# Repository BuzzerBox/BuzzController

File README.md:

# BuzzController

Firmware and hardware designs for the BuzzerBox — a 10-button quiz buzzer controller. A Raspberry Pi CM4 acts as the host, communicating with an ATmega328P co-processor over serial. The ATmega handles button detection, locks the active buzzer, and drives a 7-segment display.

[`wireless/`](wireless/README.md) holds the firmware of the wireless buzzer: a battery-powered ESP32 Feather V2 that joins the box's WiFi.

---

## Features

- **10 buzzers** with individual LED feedback, interrupt-driven detection
- **7-segment display** showing the active buzzer number and RPi connection status
- **Serial communication** with a Raspberry Pi at 115200 baud, including heartbeat monitoring
- **Soft release** — RPi can remotely unlock the selected buzzer
- **Watchdog timer** for automatic recovery from firmware hangs
- **I2C I/O expanders** (MCP23017) to drive LEDs and display

---

## Repository Structure

```
BuzzController/
├── cad/
│   └── BuzzerBox/
│       ├── controller.brd/.sch    # Main ATmega328P controller board
│       ├── xlrpcb.brd/.sch        # XLR connector board (V3)
│       ├── devkeys.brd/.sch       # Development key PCB
│       ├── ttl_adapter.brd/.sch   # TTL adapter for devkit
│       └── eagle.epf              # EAGLE CAD project file
│   └── BuzzerBoxPanel.f3d         # Fusion 360 enclosure design
├── wireless/                      # Wireless buzzer (ESP32 Feather V2), see wireless/README.md
└── code/
    ├── platformio.ini             # Build configuration
    └── src/
        ├── BuzzerBox.cpp          # Main firmware logic
        ├── i2c_communication.*    # MCP23017 I/O expander driver
        ├── rpi_communication.*    # Serial protocol with Raspberry Pi
        ├── 7segment.*             # 7-segment display driver
        └── portConfig.hpp         # Pin/port and I2C address configuration
```

---

## Hardware

| Component | Details |
|---|---|
| Host | Raspberry Pi CM4 (mounted directly on PCB) |
| Microcontroller | ATmega328P |
| I/O Expanders | 2× MCP23017 (I2C addresses `0x20`, `0x21`) |
| Display | 7-segment LED (common cathode, via expander) |
| Buttons | 10 buzzers across MCU ports B, C, D + 1 release button |
| CM4 ↔ MCU | Serial UART (115200 baud) |
| Programming | AVRISP mkII compatible (e.g. Olimex AVR-ISP-MK2) via the 6-pin ICSP header |

PCB designs are in [EAGLE](https://www.autodesk.com/products/eagle/overview) format. The enclosure panel is a [Fusion 360](https://www.autodesk.com/products/fusion-360/overview) file.

---

## Serial Protocol

Communication between the ATmega328P and the Raspberry Pi uses 3-byte UART messages at **115200 baud**:

```
[Command Byte] [Data Byte] [0xFF]
```

### Commands (RPi → Controller)

| Command | Value | Description |
|---|---|---|
| `EMPTY` | `0x00` | No operation |
| `SOFT_RELEASE` | `0x01` | Unlock the active buzzer |
| `SET_BUZZER` | `0x02` | Lock a specific buzzer (data = buzzer ID 0–9) |

### Events (Controller → RPi)

| Event | Byte | Description |
|---|---|---|
| Button pressed | `'0'`–`'9'` (ASCII) | Buzzer ID of the pressed button |
| Buzzer unlocked | `'q'` | Acknowledges an unlock |

A heartbeat is expected from the RPi every **6 seconds**. If no heartbeat is received within this window, the controller transitions to a disconnected state and reflects this on the display's decimal point.

---

## Building and Flashing

The firmware uses [PlatformIO](https://platformio.org/).

```bash
# Install PlatformIO CLI or use the VSCode extension

# Build
pio run

# Upload
pio run --target upload
```

Upload uses an AVRISP mkII compatible programmer (e.g. Olimex AVR-ISP-MK2) over USB, connected to the 6-pin ICSP header. Power the board from its own supply while flashing.

---

## Development

The `devkeys` PCB and `ttl_adapter` PCB are development accessories for testing the firmware without the full buzzer assembly.

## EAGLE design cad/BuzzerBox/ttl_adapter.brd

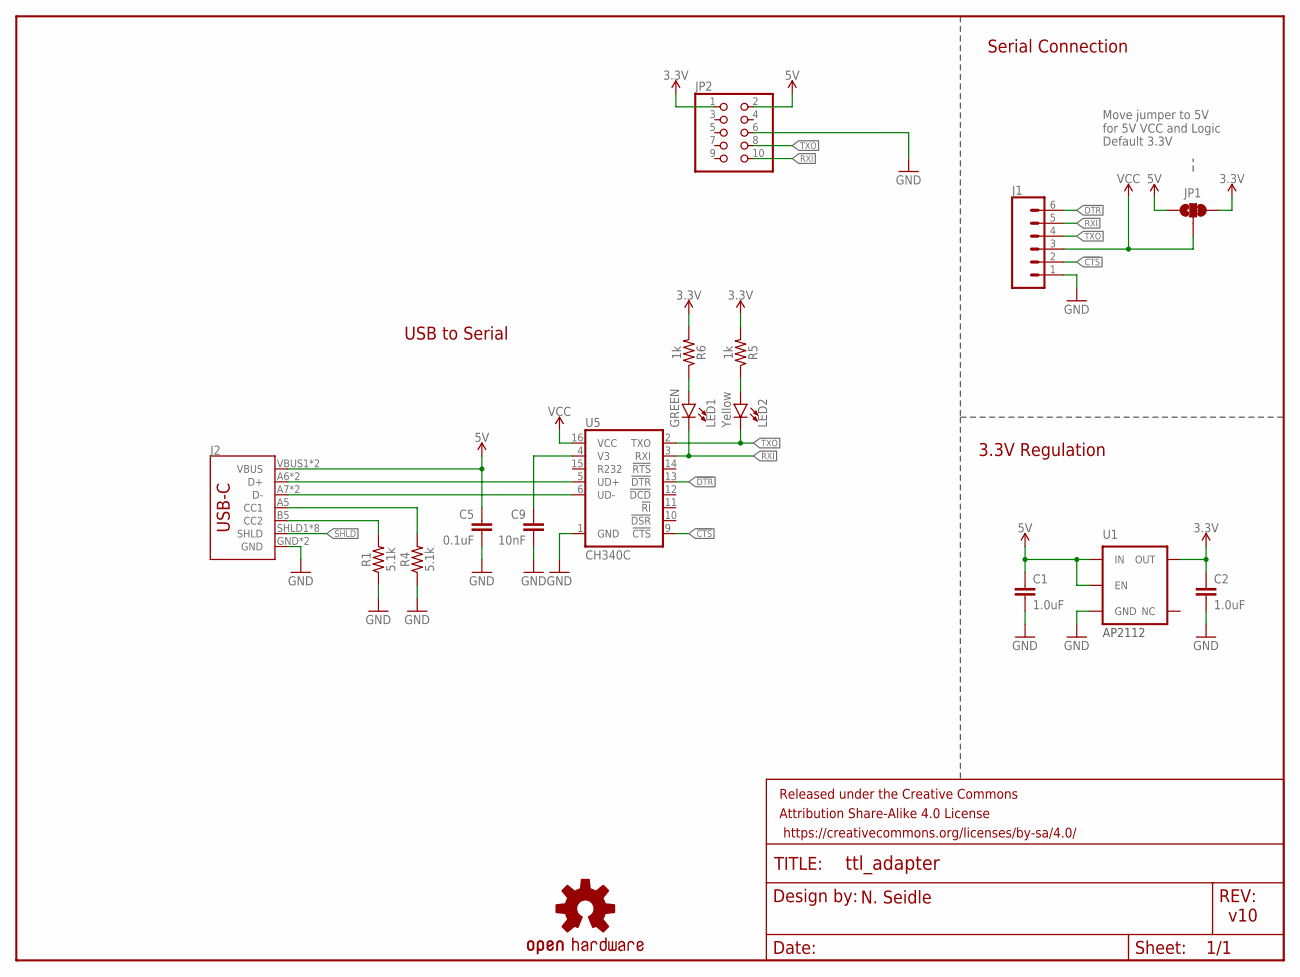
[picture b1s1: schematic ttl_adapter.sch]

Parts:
C1, C2: 1.0uF; 0603
C5: 0.1uF; 0603
C9: 10nF; 0603
FRAME1: FRAME-LETTER; CREATIVE_COMMONS
J1: CONN_06SMD-FEMALE-V2; 1X06-SMD-FEMALE
J2: USB_C16PIN; USB-C-16P
JP1: JUMPER-SMT_3_1-NC_TRACE_SILK; SMT-JUMPER_3_1-NC_TRACE_SILK
JP2: PINHD-2X5; 2X05
LED1: GREEN; LED-0603
LED2: Yellow; LED-0603
LOGO1: OSHW-LOGOS; OSHW-LOGO-S
R1, R4: 5.1k; 0603
R5, R6: 1k; 0603
U1: 3.3V; SOT23-5
U5: CH340C; SO016

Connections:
3.3V: C2.1, JP1.3, JP2.1, R5.2, R6.2, U1.5 (OUT)
5V: C1.1, C5.1, J2.VBUS1 (VBUS), J2.VBUS2 (VBUS), JP1.1, JP2.2, U1.1 (IN), U1.3 (EN)
!CTS: J1.2, U5.9 (!CTS)
!DTR: J1.6, U5.13 (!DTR)
CC1: J2.A5 (CC1), R4.2
CC2: J2.B5 (CC2), R1.2
D+: J2.A6 (D+), J2.B6 (D+), U5.5 (UD+)
D-: J2.A7 (D-), J2.B7 (D-), U5.6 (UD-)
GND: C1.2, C2.2, C5.2, C9.2, J1.1, J2.GND, J2.GND2 (GND), JP2.6, R1.1, R4.1, U1.2 (GND), U5.1 (GND)
unnamed: C9.1, U5.4 (V3)
unnamed: LED1.A, R6.1
unnamed: LED2.A, R5.1
RXI: J1.5, JP2.10, LED1.C, U5.3 (RXI)
SHLD: J2.SHLD1 (SHLD), J2.SHLD2 (SHLD), J2.SHLD3 (SHLD), J2.SHLD4 (SHLD), J2.SHLD5 (SHLD), J2.SHLD6 (SHLD), J2.SHLD7 (SHLD), J2.SHLD8 (SHLD)
TXO: J1.4, JP2.8, LED2.C, U5.2 (TXO)
VCC: J1.3, JP1.2, U5.16 (VCC)

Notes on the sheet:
Default 3.3V
v10
USB to Serial
3.3V Regulation
N. Seidle
Move jumper to 5V for 5V VCC and Logic
Serial Connection
AP2112

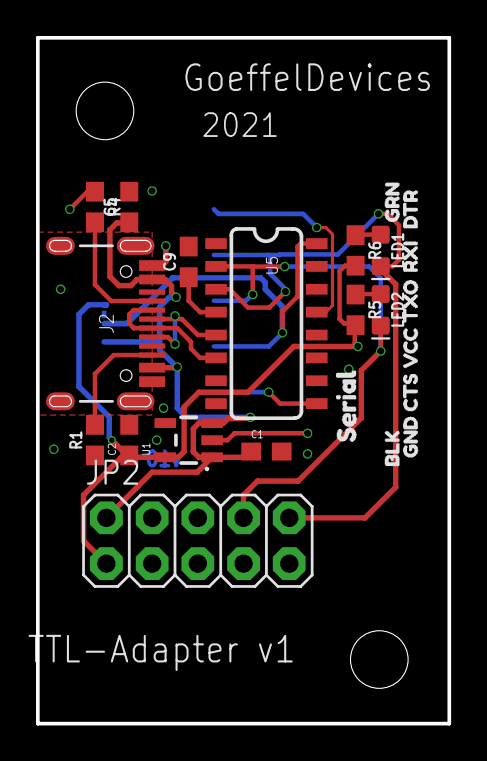
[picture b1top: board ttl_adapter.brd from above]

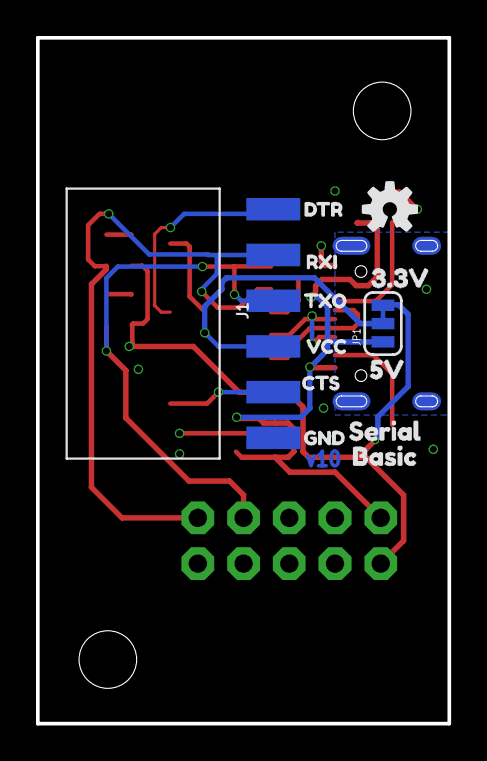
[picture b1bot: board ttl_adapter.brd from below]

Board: 2 copper layers, 22.9 x 38.1 mm, 39 parts (13 on the bottom side), 16 nets.

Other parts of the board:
U$1, U$14: CTS1
U$2: 3#3V8
U$3: 5V9
U$4, U$9: SERIAL0
U$5, U$12: TXO0
U$6, U$13: VCC2
U$8, U$18: DTR0
U$10, U$21: RXI1
U$11: BASIC1
U$15, U$19: GND5
U$16, U$22: M3-HOLE
U$17: BLK6
U$20: GRN7

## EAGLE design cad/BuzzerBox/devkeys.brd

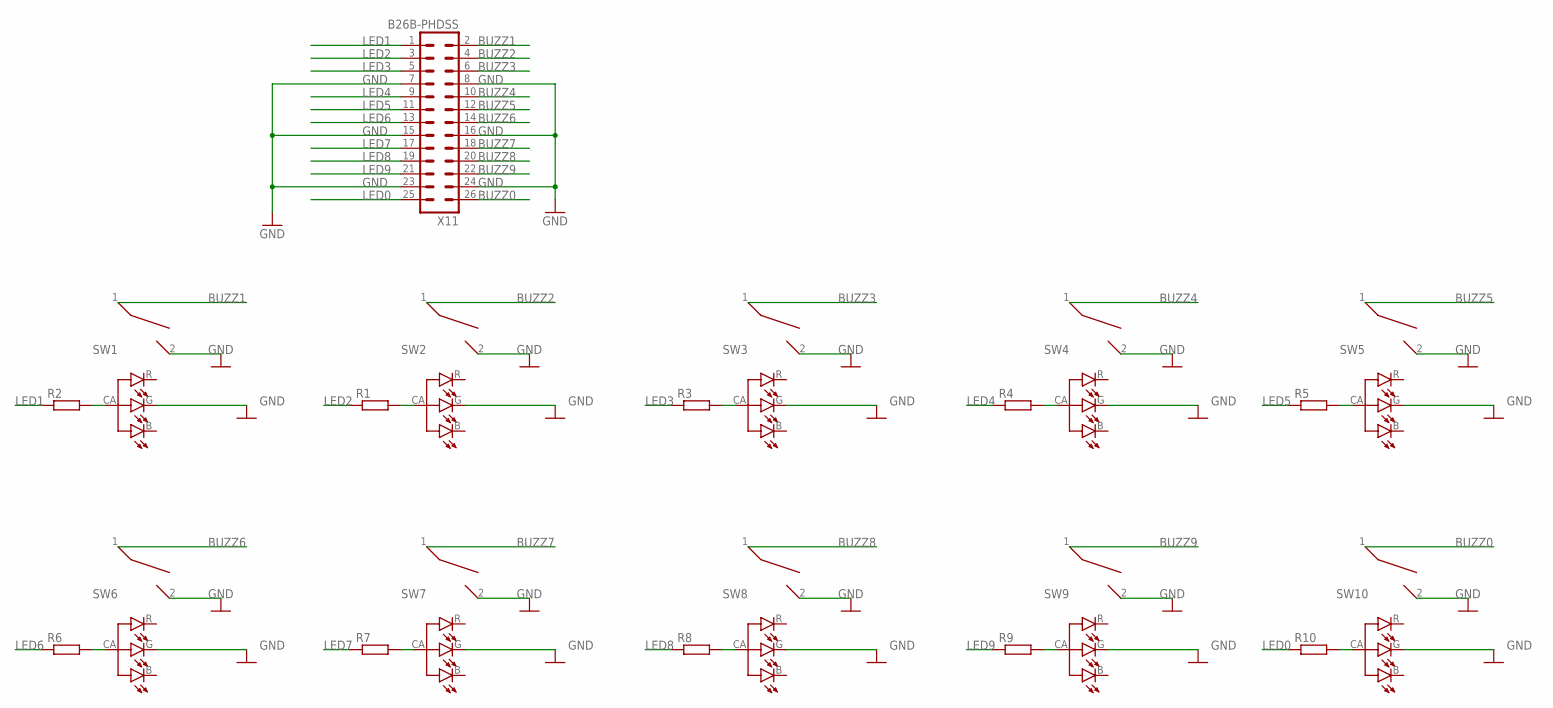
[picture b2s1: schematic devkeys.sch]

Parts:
R1, R2, R3, R4, R5, R6, R7, R8, R9, R10: R-EU_R0805; R0805
SW1, SW2, SW3, SW4, SW5, SW6, SW7, SW8, SW9, SW10: ZEALIOS; ZEALIOS-PCB_1U
X11: B26B-PHDSS

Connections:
BUZZ0: SW10.1, X11.26
BUZZ1: SW1.1, X11.2
BUZZ2: SW2.1, X11.4
BUZZ3: SW3.1, X11.6
BUZZ4: SW4.1, X11.10
BUZZ5: SW5.1, X11.12
BUZZ6: SW6.1, X11.14
BUZZ7: SW7.1, X11.18
BUZZ8: SW8.1, X11.20
BUZZ9: SW9.1, X11.22
GND: SW1.2, SW1.G (G-CAT), SW2.2, SW2.G (G-CAT), SW3.2, SW3.G (G-CAT), SW4.2, SW4.G (G-CAT), SW5.2, SW5.G (G-CAT), SW6.2, SW6.G (G-CAT), SW7.2, SW7.G (G-CAT), SW8.2, SW8.G (G-CAT), SW9.2, SW9.G (G-CAT), SW10.2, SW10.G (G-CAT), X11.7, X11.8, X11.15, X11.16, X11.23, X11.24
LED0: R10.1, X11.25
LED1: R2.1, X11.1
LED2: R1.1, X11.3
LED3: R3.1, X11.5
LED4: R4.1, X11.9
LED5: R5.1, X11.11
LED6: R6.1, X11.13
LED7: R7.1, X11.17
LED8: R8.1, X11.19
LED9: R9.1, X11.21
unnamed: R1.2, SW2.CA (COMMON-ANODE)
unnamed: R2.2, SW1.CA (COMMON-ANODE)
unnamed: R3.2, SW3.CA (COMMON-ANODE)
unnamed: R4.2, SW4.CA (COMMON-ANODE)
unnamed: R5.2, SW5.CA (COMMON-ANODE)
unnamed: R6.2, SW6.CA (COMMON-ANODE)
unnamed: R7.2, SW7.CA (COMMON-ANODE)
unnamed: R8.2, SW8.CA (COMMON-ANODE)
unnamed: R9.2, SW9.CA (COMMON-ANODE)
unnamed: R10.2, SW10.CA (COMMON-ANODE)

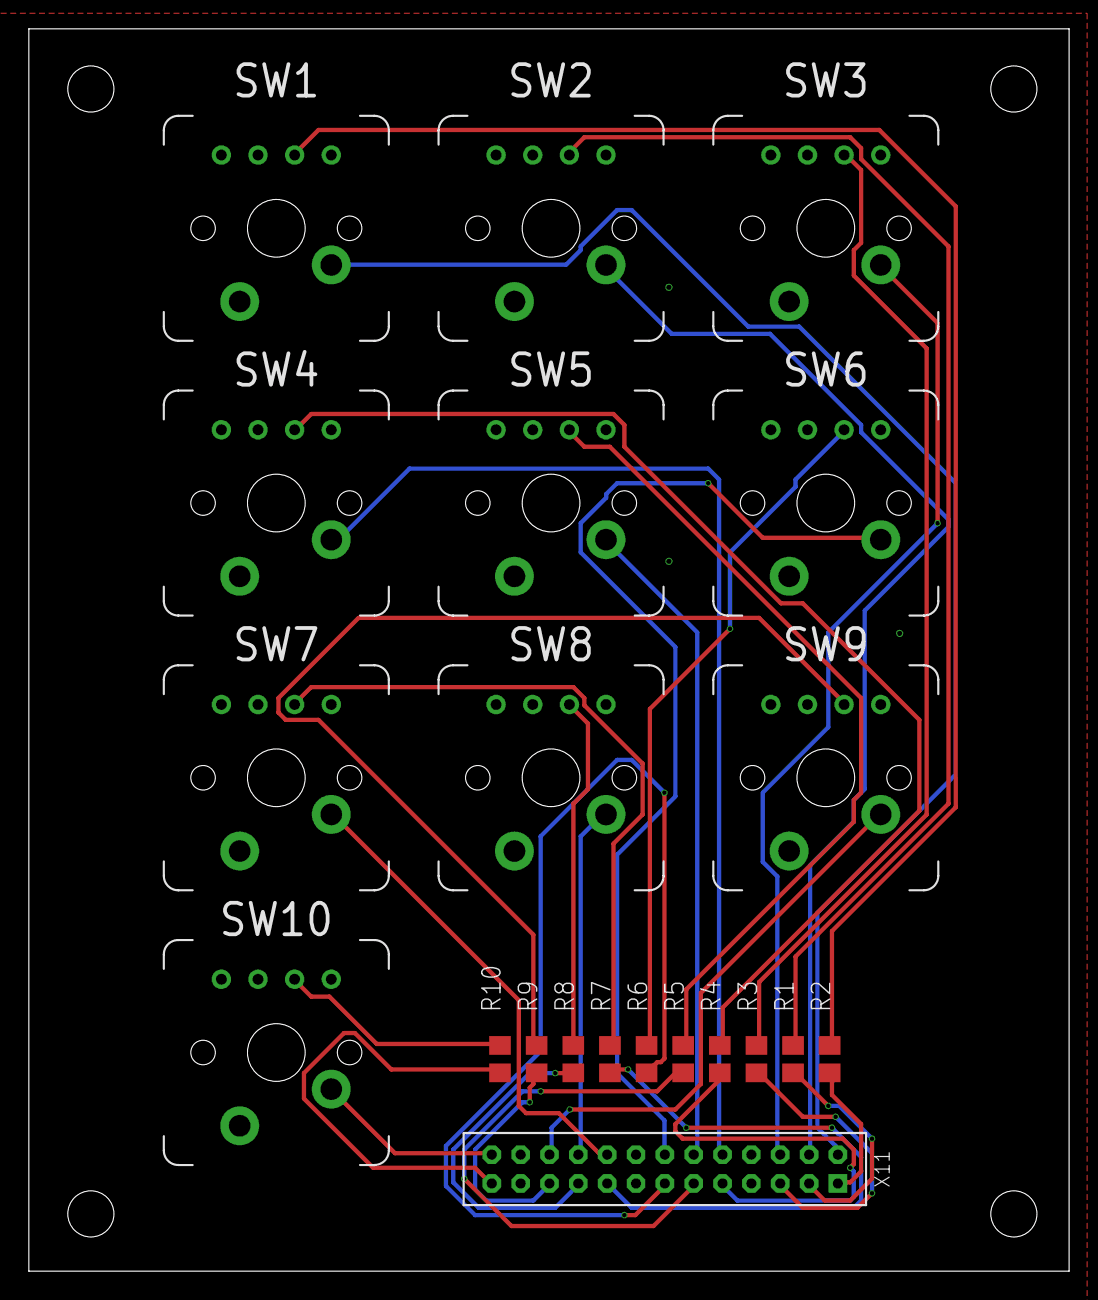
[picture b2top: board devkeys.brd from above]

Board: 2 copper layers, 72.1 x 86.1 mm, 25 parts (0 on the bottom side), 31 nets.

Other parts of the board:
U$1, U$2, U$3, U$4: M3-HOLE

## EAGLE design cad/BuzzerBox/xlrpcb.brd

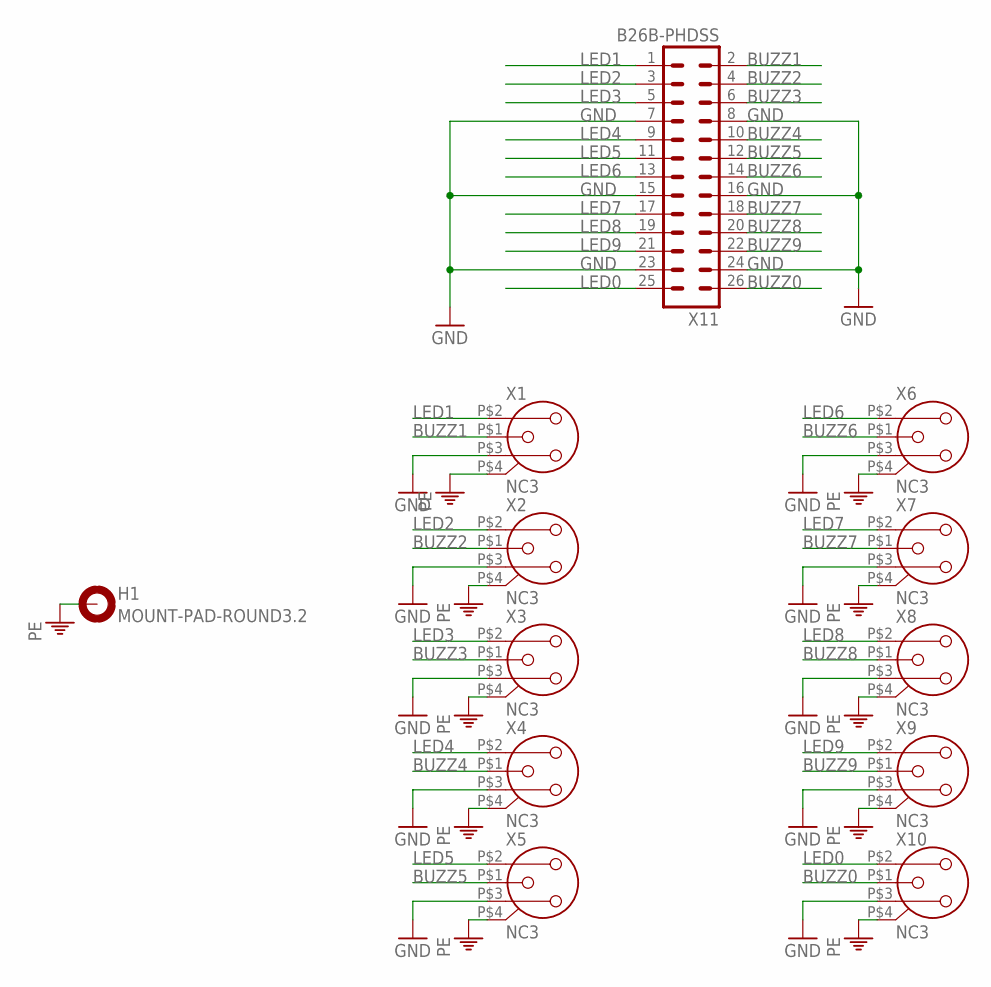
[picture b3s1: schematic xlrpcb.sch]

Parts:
H1: MOUNT-PAD-ROUND3.2; 3,2-PAD
X1, X2, X3, X4, X5, X6, X7, X8, X9, X10: NC3; NC3FD-X
X11: B26B-PHDSS

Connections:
BUZZ0: X10.P$1 (3), X11.26
BUZZ1: X1.P$1 (3), X11.2
BUZZ2: X2.P$1 (3), X11.4
BUZZ3: X3.P$1 (3), X11.6
BUZZ4: X4.P$1 (3), X11.10
BUZZ5: X5.P$1 (3), X11.12
BUZZ6: X6.P$1 (3), X11.14
BUZZ7: X7.P$1 (3), X11.18
BUZZ8: X8.P$1 (3), X11.20
BUZZ9: X9.P$1 (3), X11.22
GND: X1.P$3 (2), X2.P$3 (2), X3.P$3 (2), X4.P$3 (2), X5.P$3 (2), X6.P$3 (2), X7.P$3 (2), X8.P$3 (2), X9.P$3 (2), X10.P$3 (2), X11.7, X11.8, X11.15, X11.16, X11.23, X11.24
LED0: X10.P$2 (1), X11.25
LED1: X1.P$2 (1), X11.1
LED2: X2.P$2 (1), X11.3
LED3: X3.P$2 (1), X11.5
LED4: X4.P$2 (1), X11.9
LED5: X5.P$2 (1), X11.11
LED6: X6.P$2 (1), X11.13
LED7: X7.P$2 (1), X11.17
LED8: X8.P$2 (1), X11.19
LED9: X9.P$2 (1), X11.21
PE: H1.B3,2, X1.P$4 (G), X2.P$4 (G), X3.P$4 (G), X4.P$4 (G), X5.P$4 (G), X6.P$4 (G), X7.P$4 (G), X8.P$4 (G), X9.P$4 (G), X10.P$4 (G)

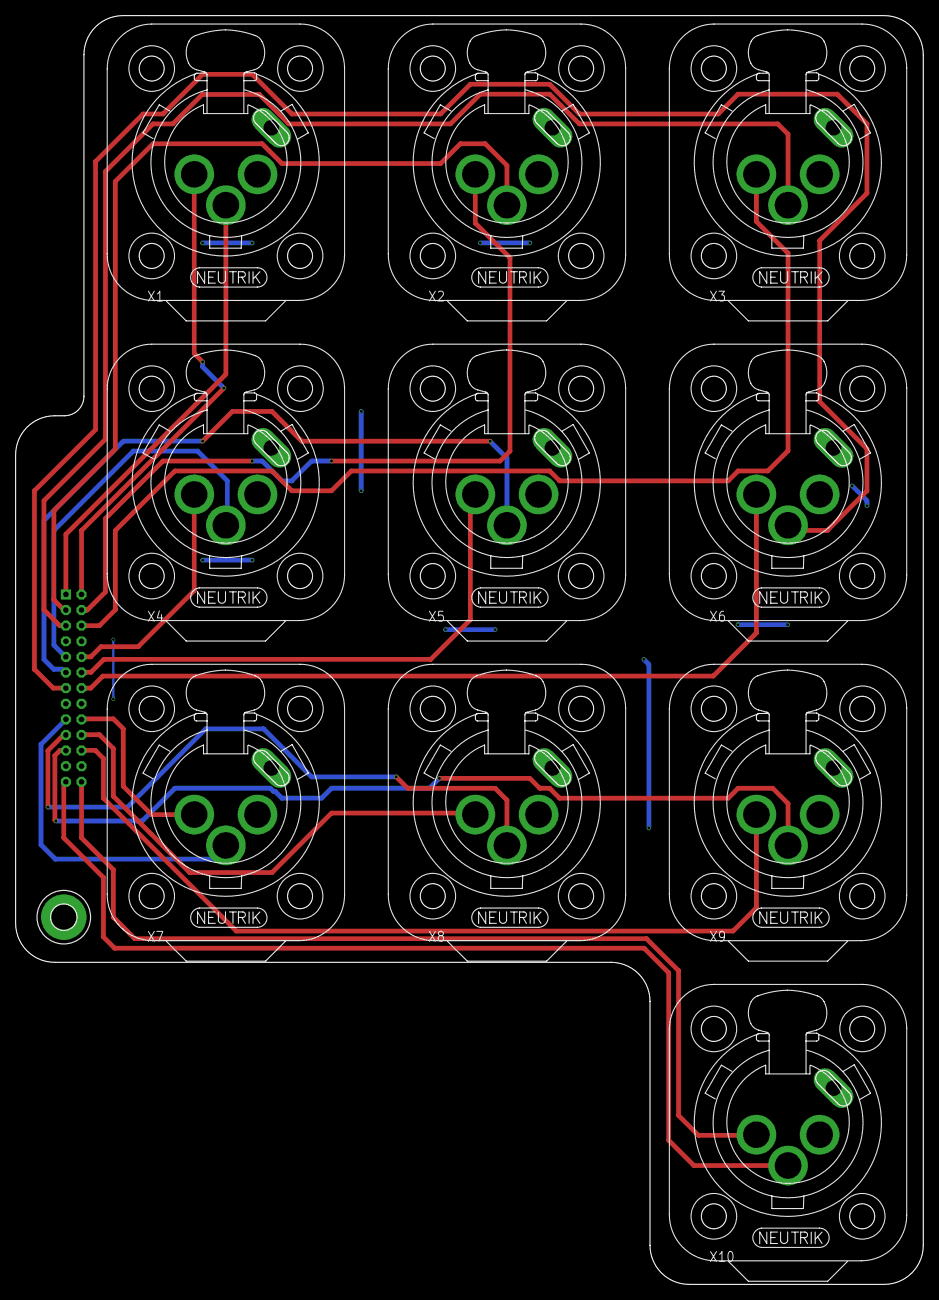
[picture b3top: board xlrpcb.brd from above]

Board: 2 copper layers, 116.2 x 162.5 mm, 12 parts (1 on the bottom side), 22 nets.

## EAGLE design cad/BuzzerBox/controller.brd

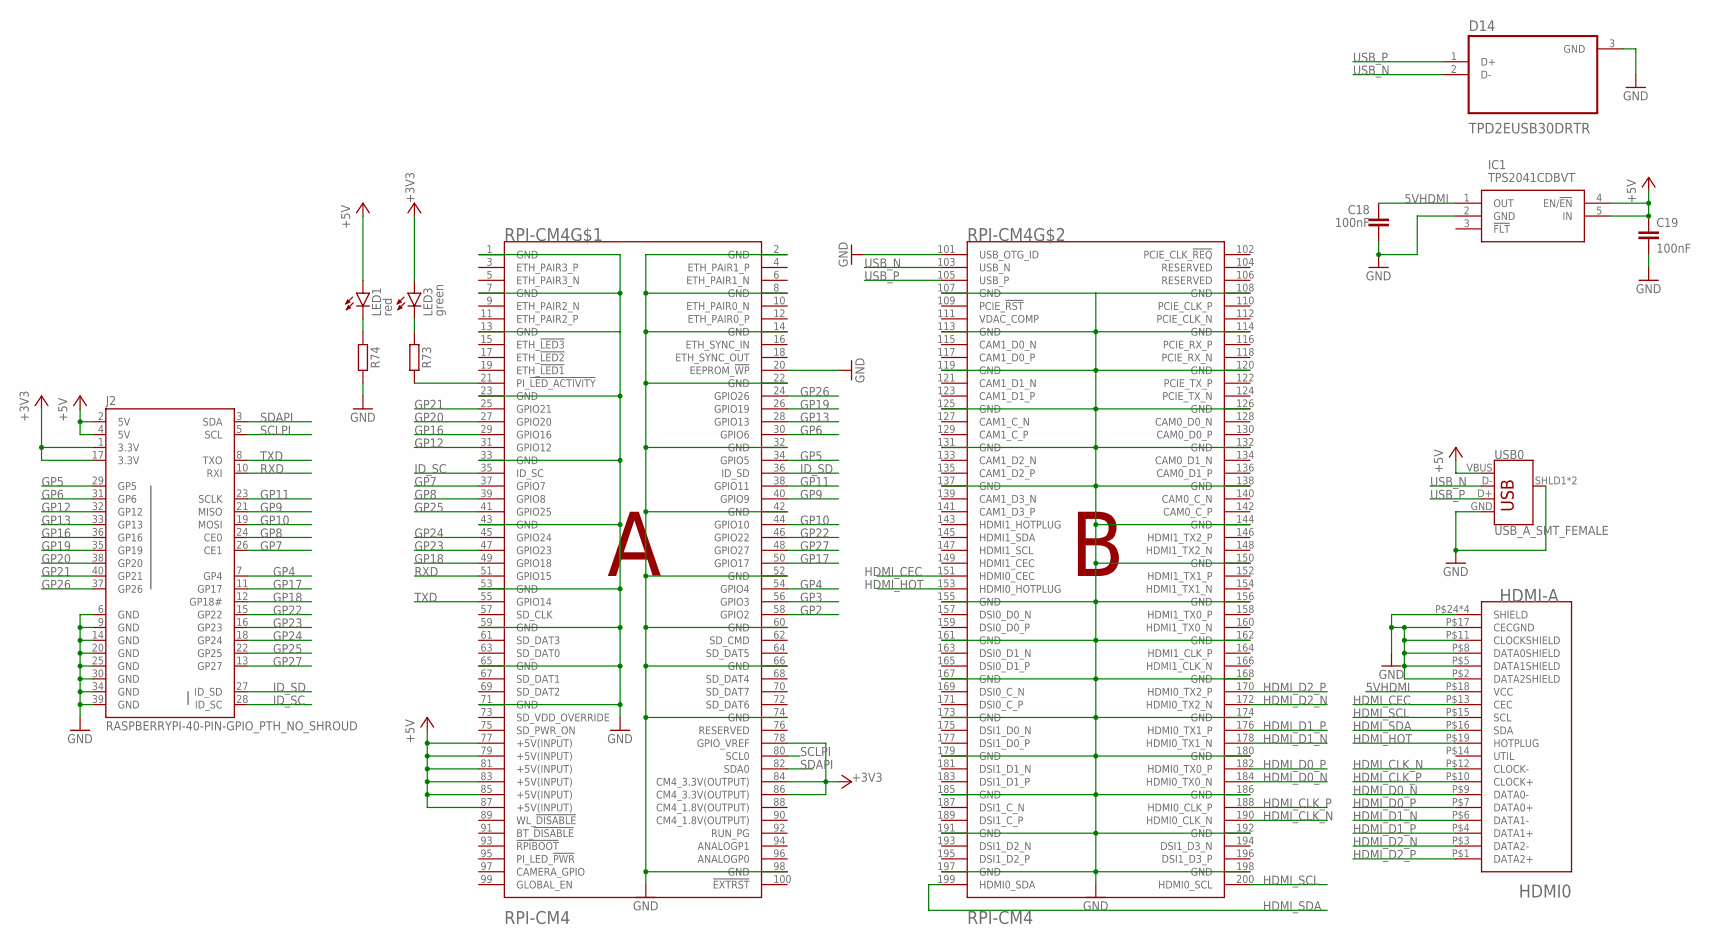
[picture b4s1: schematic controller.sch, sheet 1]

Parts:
C18, C19: 100nF; C0805
D14: TPD2EUSB30DRTR; SOTFL35P100X50-3N
HDMI0: HDMI-A; HDMI_A
IC1: TPS2041CDBVT; SOT95P280X145-5N
J2: RASPBERRYPI-40-PIN-GPIO_PTH_NO_SHROUD; 2X20
LED1: red; CHIP-LED0805
LED3: green; CHIP-LED0805
R73, R74: 1k; R0805
RPI-CM4: RPI-CM4
USB0: USB_A_SMT_FEMALE; USB-A-S-SILK-FEMALE

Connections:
5VHDMI: C18.1, HDMI0.P$18 (VCC), IC1.1 (OUT)
+3V3: J2.1 (3.3V), J2.17 (3.3V), LED3.A, RPI-CM4.78 (GPIO_VREF), RPI-CM4.84 (CM4_3.3V(OUTPUT)), RPI-CM4.86 (CM4_3.3V(OUTPUT)); also elsewhere on the board
+5V: C19.1, IC1.4 (EN/!EN), IC1.5 (IN), J2.2 (5V), J2.4 (5V), LED1.A, RPI-CM4.77 (+5V(INPUT)), RPI-CM4.79 (+5V(INPUT)), RPI-CM4.81 (+5V(INPUT)), RPI-CM4.83 (+5V(INPUT)), RPI-CM4.85 (+5V(INPUT)), RPI-CM4.87 (+5V(INPUT)), USB0.VBUS; also elsewhere on the board
GND: C18.2, C19.2, D14.3 (GND), HDMI0.P$2 (DATA2SHIELD), HDMI0.P$5 (DATA1SHIELD), HDMI0.P$8 (DATA0SHIELD), HDMI0.P$11 (CLOCKSHIELD), HDMI0.P$17 (CECGND), HDMI0.P$24 (SHIELD), HDMI0.P$25 (SHIELD), HDMI0.P$26 (SHIELD), HDMI0.P$27 (SHIELD), IC1.2 (GND), J2.6 (GND), J2.9 (GND), J2.14 (GND), J2.20 (GND), J2.25 (GND), J2.30 (GND), J2.34 (GND), J2.39 (GND), R74.2, RPI-CM4.1 (GND), RPI-CM4.2 (GND), RPI-CM4.7 (GND), RPI-CM4.8 (GND), RPI-CM4.13 (GND), RPI-CM4.14 (GND), RPI-CM4.20 (EEPROM_!WP), RPI-CM4.22 (GND), RPI-CM4.23 (GND), RPI-CM4.32 (GND), RPI-CM4.33 (GND), RPI-CM4.42 (GND), RPI-CM4.43 (GND), RPI-CM4.52 (GND), RPI-CM4.53 (GND), RPI-CM4.59 (GND), RPI-CM4.60 (GND), RPI-CM4.65 (GND), RPI-CM4.66 (GND), RPI-CM4.71 (GND), RPI-CM4.74 (GND), RPI-CM4.98 (GND), RPI-CM4.101 (USB_OTG_ID), RPI-CM4.107 (GND), RPI-CM4.108 (GND), RPI-CM4.113 (GND), RPI-CM4.114 (GND), RPI-CM4.119 (GND), RPI-CM4.120 (GND), RPI-CM4.125 (GND), RPI-CM4.126 (GND), RPI-CM4.131 (GND), RPI-CM4.132 (GND), RPI-CM4.137 (GND), RPI-CM4.138 (GND), RPI-CM4.144 (GND), RPI-CM4.150 (GND), RPI-CM4.155 (GND), RPI-CM4.156 (GND), RPI-CM4.161 (GND), RPI-CM4.162 (GND), RPI-CM4.167 (GND), RPI-CM4.168 (GND), RPI-CM4.173 (GND), RPI-CM4.174 (GND), RPI-CM4.179 (GND), RPI-CM4.180 (GND), RPI-CM4.185 (GND), RPI-CM4.186 (GND), RPI-CM4.191 (GND), RPI-CM4.192 (GND), RPI-CM4.197 (GND), RPI-CM4.198 (GND), USB0.GND, USB0.SHLD1 (SHIELD), USB0.SHLD2 (SHIELD); also elsewhere on the board
GP2: RPI-CM4.58 (GPIO2)
GP3: RPI-CM4.56 (GPIO3)
GP4: J2.7 (GP4), RPI-CM4.54 (GPIO4)
GP5: J2.29 (GP5), RPI-CM4.34 (GPIO5)
GP6: J2.31 (GP6), RPI-CM4.30 (GPIO6)
GP7: J2.26 (CE1), RPI-CM4.37 (GPIO7)
GP8: J2.24 (CE0), RPI-CM4.39 (GPIO8)
GP9: J2.21 (MISO), RPI-CM4.40 (GPIO9)
GP10: J2.19 (MOSI), RPI-CM4.44 (GPIO10)
GP11: J2.23 (SCLK), RPI-CM4.38 (GPIO11)
GP12: J2.32 (GP12), RPI-CM4.31 (GPIO12)
GP13: J2.33 (GP13), RPI-CM4.28 (GPIO13)
GP16: J2.36 (GP16), RPI-CM4.29 (GPIO16)
GP17: J2.11 (GP17), RPI-CM4.50 (GPIO17)
GP18: J2.12 (GP18#), RPI-CM4.49 (GPIO18)
GP19: J2.35 (GP19), RPI-CM4.26 (GPIO19)
GP20: J2.38 (GP20), RPI-CM4.27 (GPIO20)
GP21: J2.40 (GP21), RPI-CM4.25 (GPIO21)
GP22: J2.15 (GP22), RPI-CM4.46 (GPIO22)
GP23: J2.16 (GP23), RPI-CM4.47 (GPIO23); also elsewhere on the board
GP24: J2.18 (GP24), RPI-CM4.45 (GPIO24)
GP25: J2.22 (GP25), RPI-CM4.41 (GPIO25)
GP26: J2.37 (GP26), RPI-CM4.24 (GPIO26)
GP27: J2.13 (GP27), RPI-CM4.48 (GPIO27)
HDMI_CEC: HDMI0.P$13 (CEC), RPI-CM4.151 (HDMI0_CEC)
HDMI_CLK_N: HDMI0.P$12 (CLOCK-), RPI-CM4.190 (HDMI0_CLK_N)
HDMI_CLK_P: HDMI0.P$10 (CLOCK+), RPI-CM4.188 (HDMI0_CLK_P)
HDMI_D0_N: HDMI0.P$9 (DATA0-), RPI-CM4.184 (HDMI0_TX0_N)
HDMI_D0_P: HDMI0.P$7 (DATA0+), RPI-CM4.182 (HDMI0_TX0_P)
HDMI_D1_N: HDMI0.P$6 (DATA1-), RPI-CM4.178 (HDMI0_TX1_N)
HDMI_D1_P: HDMI0.P$4 (DATA1+), RPI-CM4.176 (HDMI0_TX1_P)
HDMI_D2_N: HDMI0.P$3 (DATA2-), RPI-CM4.172 (HDMI0_TX2_N)
HDMI_D2_P: HDMI0.P$1 (DATA2+), RPI-CM4.170 (HDMI0_TX2_P)
HDMI_HOT: HDMI0.P$19 (HOTPLUG), RPI-CM4.153 (HDMI0_HOTPLUG)
HDMI_SCL: HDMI0.P$15 (SCL), RPI-CM4.200 (HDMI0_SCL)
HDMI_SDA: HDMI0.P$16 (SDA), RPI-CM4.199 (HDMI0_SDA)
ID_SC: J2.28 (ID_SC), RPI-CM4.35 (ID_SC)
ID_SD: J2.27 (ID_SD), RPI-CM4.36 (ID_SD)
unnamed: R73.2, RPI-CM4.21 (PI_!LED_ACTIVITY)
unnamed: LED3.C, R73.1
unnamed: LED1.C, R74.1
RXD: J2.10 (RXI), RPI-CM4.51 (GPIO15); also elsewhere on the board
SCLPI: J2.5 (SCL), RPI-CM4.80 (SCL0)
SDAPI: J2.3 (SDA), RPI-CM4.82 (SDA0)
TXD: J2.8 (TXO), RPI-CM4.55 (GPIO14); also elsewhere on the board
USB_N: D14.2 (D-), RPI-CM4.103 (USB_N), USB0.D-
USB_P: D14.1 (D+), RPI-CM4.105 (USB_P), USB0.D+

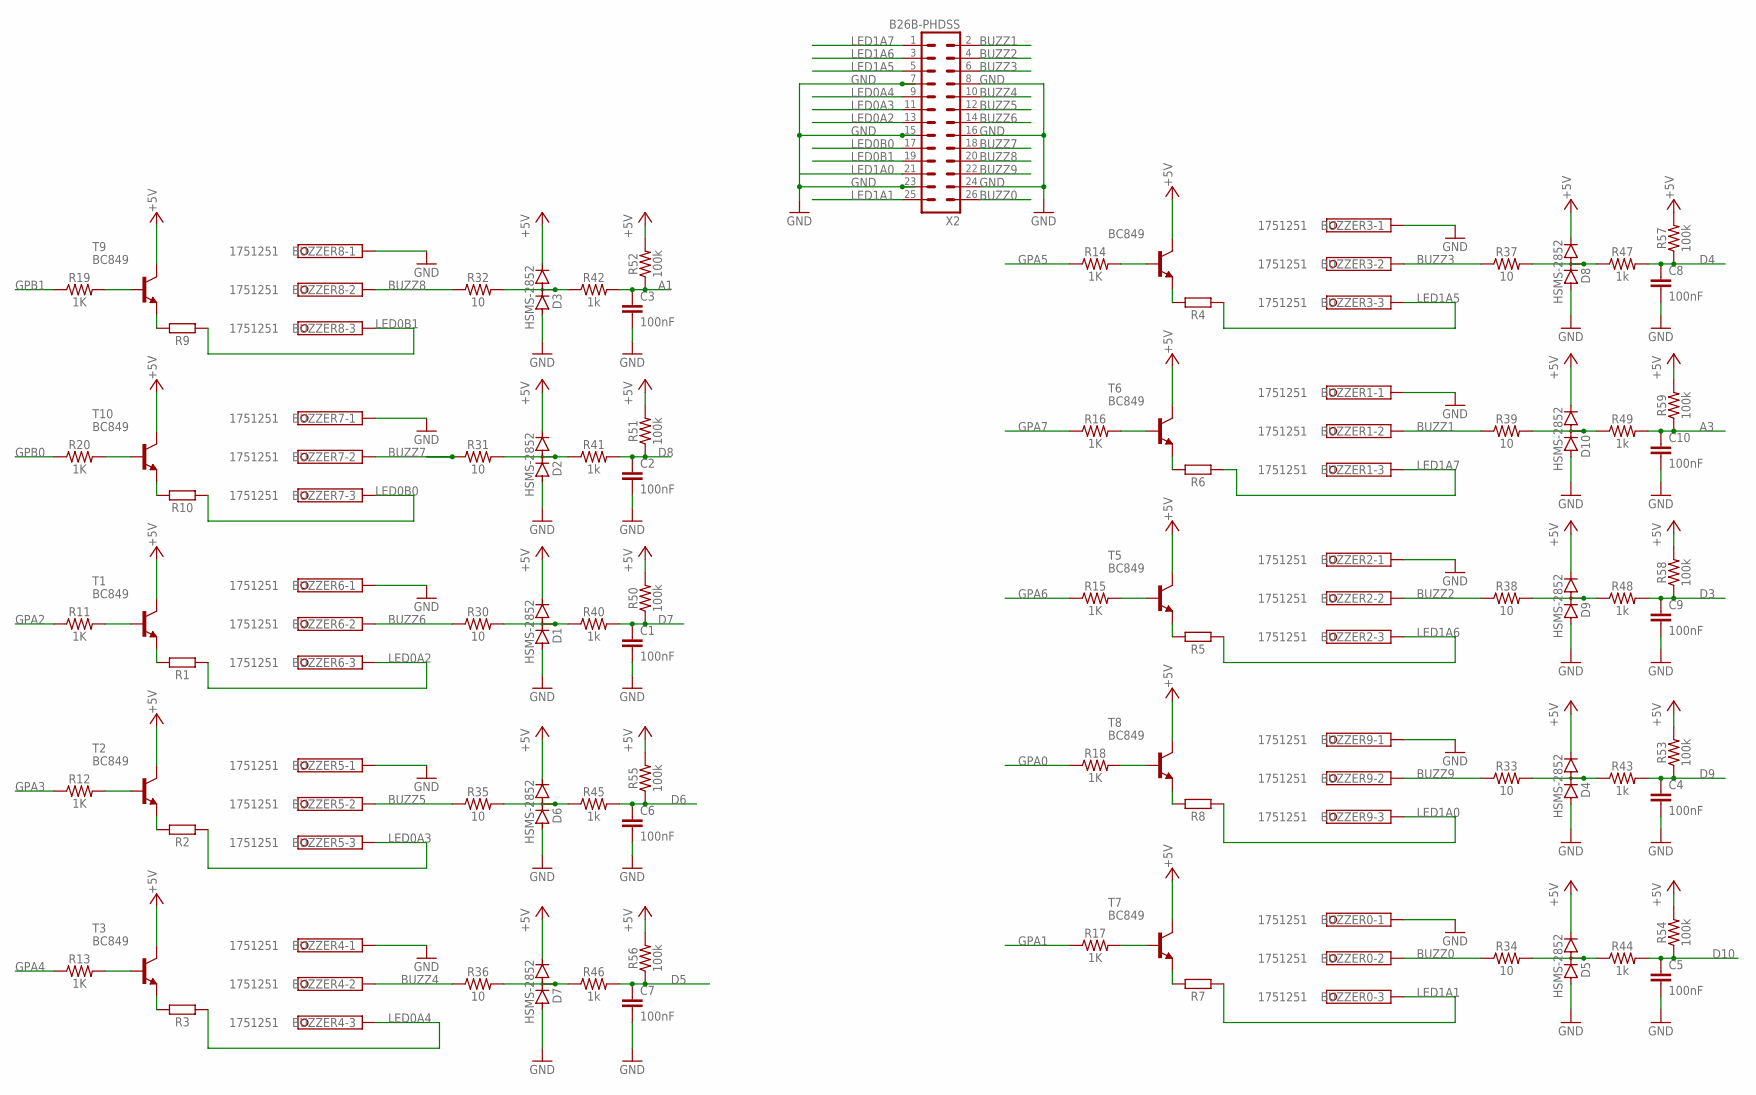
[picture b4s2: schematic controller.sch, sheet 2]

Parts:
BUZZER0, BUZZER1, BUZZER2, BUZZER3, BUZZER4, BUZZER5, BUZZER6, BUZZER7, BUZZER8, BUZZER9: 1751251
C1, C2, C3, C4, C5, C6, C7, C8, C9, C10: 100nF; C0805
D1, D2, D3, D4, D5, D6, D7, D8, D9, D10: HSMS-2852; SOT23
R1, R2, R3, R4, R5, R6, R7, R8, R9, R10: 50; R2512
R11, R12, R13, R14, R15, R16, R17, R18, R19, R20: 1K; 0805
R30, R31, R32, R33, R34, R35, R36, R37, R38, R39: 10; 0805
R40, R41, R42, R43, R44, R45, R46, R47, R48, R49: 1k; 0805
R50, R51, R52, R53, R54, R55, R56, R57, R58, R59: 100k; 0805
T1, T2, T3, T4, T5, T6, T7, T8, T9, T10: BC849; SOT23
X2: B26B-PHDSS

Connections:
+5V: D1.2 (C), D2.2 (C), D3.2 (C), D4.2 (C), D5.2 (C), D6.2 (C), D7.2 (C), D8.2 (C), D9.2 (C), D10.2 (C), R50.2, R51.2, R52.2, R53.2, R54.2, R55.2, R56.2, R57.2, R58.2, R59.2, T1.3 (C), T2.3 (C), T3.3 (C), T4.3 (C), T5.3 (C), T6.3 (C), T7.3 (C), T8.3 (C), T9.3 (C), T10.3 (C); also elsewhere on the board
A1: C3.1, R42.2, R52.1; also elsewhere on the board
A3: C10.1, R49.2, R59.1; also elsewhere on the board
BUZZ0: BUZZER0.2, R34.1, X2.26
BUZZ1: BUZZER1.2, R39.1, X2.2
BUZZ2: BUZZER2.2, R38.1, X2.4
BUZZ3: BUZZER3.2, R37.1, X2.6
BUZZ4: BUZZER4.2, R36.1, X2.10
BUZZ5: BUZZER5.2, R35.1, X2.12
BUZZ6: BUZZER6.2, R30.1, X2.14
BUZZ7: BUZZER7.2, R31.1, X2.18
BUZZ8: BUZZER8.2, R32.1, X2.20
BUZZ9: BUZZER9.2, R33.1, X2.22
D3: C9.1, R48.2, R58.1; also elsewhere on the board
D4: C8.1, R47.2, R57.1; also elsewhere on the board
D5: C7.1, R46.2, R56.1; also elsewhere on the board
D6: C6.1, R45.2, R55.1; also elsewhere on the board
D7: C1.1, R40.2, R50.1; also elsewhere on the board
D8: C2.1, R41.2, R51.1; also elsewhere on the board
D9: C4.1, R43.2, R53.1; also elsewhere on the board
D10: C5.1, R44.2, R54.1; also elsewhere on the board
GND: BUZZER0.1, BUZZER1.1, BUZZER2.1, BUZZER3.1, BUZZER4.1, BUZZER5.1, BUZZER6.1, BUZZER7.1, BUZZER8.1, BUZZER9.1, C1.2, C2.2, C3.2, C4.2, C5.2, C6.2, C7.2, C8.2, C9.2, C10.2, D1.1 (A), D2.1 (A), D3.1 (A), D4.1 (A), D5.1 (A), D6.1 (A), D7.1 (A), D8.1 (A), D9.1 (A), D10.1 (A), X2.7, X2.8, X2.15, X2.16, X2.23, X2.24; also elsewhere on the board
GPA0: R18.1; also elsewhere on the board
GPA1: R17.1; also elsewhere on the board
GPA2: R11.1; also elsewhere on the board
GPA3: R12.1; also elsewhere on the board
GPA4: R13.1; also elsewhere on the board
GPA5: R14.1; also elsewhere on the board
GPA6: R15.1; also elsewhere on the board
GPA7: R16.1; also elsewhere on the board
GPB0: R20.1; also elsewhere on the board
GPB1: R19.1; also elsewhere on the board
LED0A2: BUZZER6.3, R1.1, X2.13
LED0A3: BUZZER5.3, R2.1, X2.11
LED0A4: BUZZER4.3, R3.1, X2.9
LED0B0: BUZZER7.3, R10.1, X2.17
LED0B1: BUZZER8.3, R9.1, X2.19
LED1A0: BUZZER9.3, R8.1, X2.21
LED1A1: BUZZER0.3, R7.1, X2.25
LED1A5: BUZZER3.3, R4.1, X2.5
LED1A6: BUZZER2.3, R5.1, X2.3
LED1A7: BUZZER1.3, R6.1, X2.1
unnamed: R14.2, T4.1 (B)
unnamed: R4.2, T4.2 (E)
unnamed: D3.3 (AC), R32.2, R42.1
unnamed: R16.2, T6.1 (B)
unnamed: D2.3 (AC), R31.2, R41.1
unnamed: D8.3 (AC), R37.2, R47.1
unnamed: R6.2, T6.2 (E)
unnamed: D1.3 (AC), R30.2, R40.1
unnamed: R15.2, T5.1 (B)
unnamed: R5.2, T5.2 (E)
unnamed: D6.3 (AC), R35.2, R45.1
unnamed: D10.3 (AC), R39.2, R49.1
unnamed: R18.2, T8.1 (B)
unnamed: D7.3 (AC), R36.2, R46.1
unnamed: R8.2, T8.2 (E)
unnamed: D9.3 (AC), R38.2, R48.1
unnamed: R17.2, T7.1 (B)
unnamed: D4.3 (AC), R33.2, R43.1
unnamed: R7.2, T7.2 (E)
unnamed: R19.2, T9.1 (B)
unnamed: R9.2, T9.2 (E)
unnamed: R20.2, T10.1 (B)
unnamed: R10.2, T10.2 (E)
unnamed: R11.2, T1.1 (B)
unnamed: R1.2, T1.2 (E)
unnamed: R12.2, T2.1 (B)
unnamed: R2.2, T2.2 (E)
unnamed: R13.2, T3.1 (B)
unnamed: R3.2, T3.2 (E)
unnamed: D5.3 (AC), R34.2, R44.1

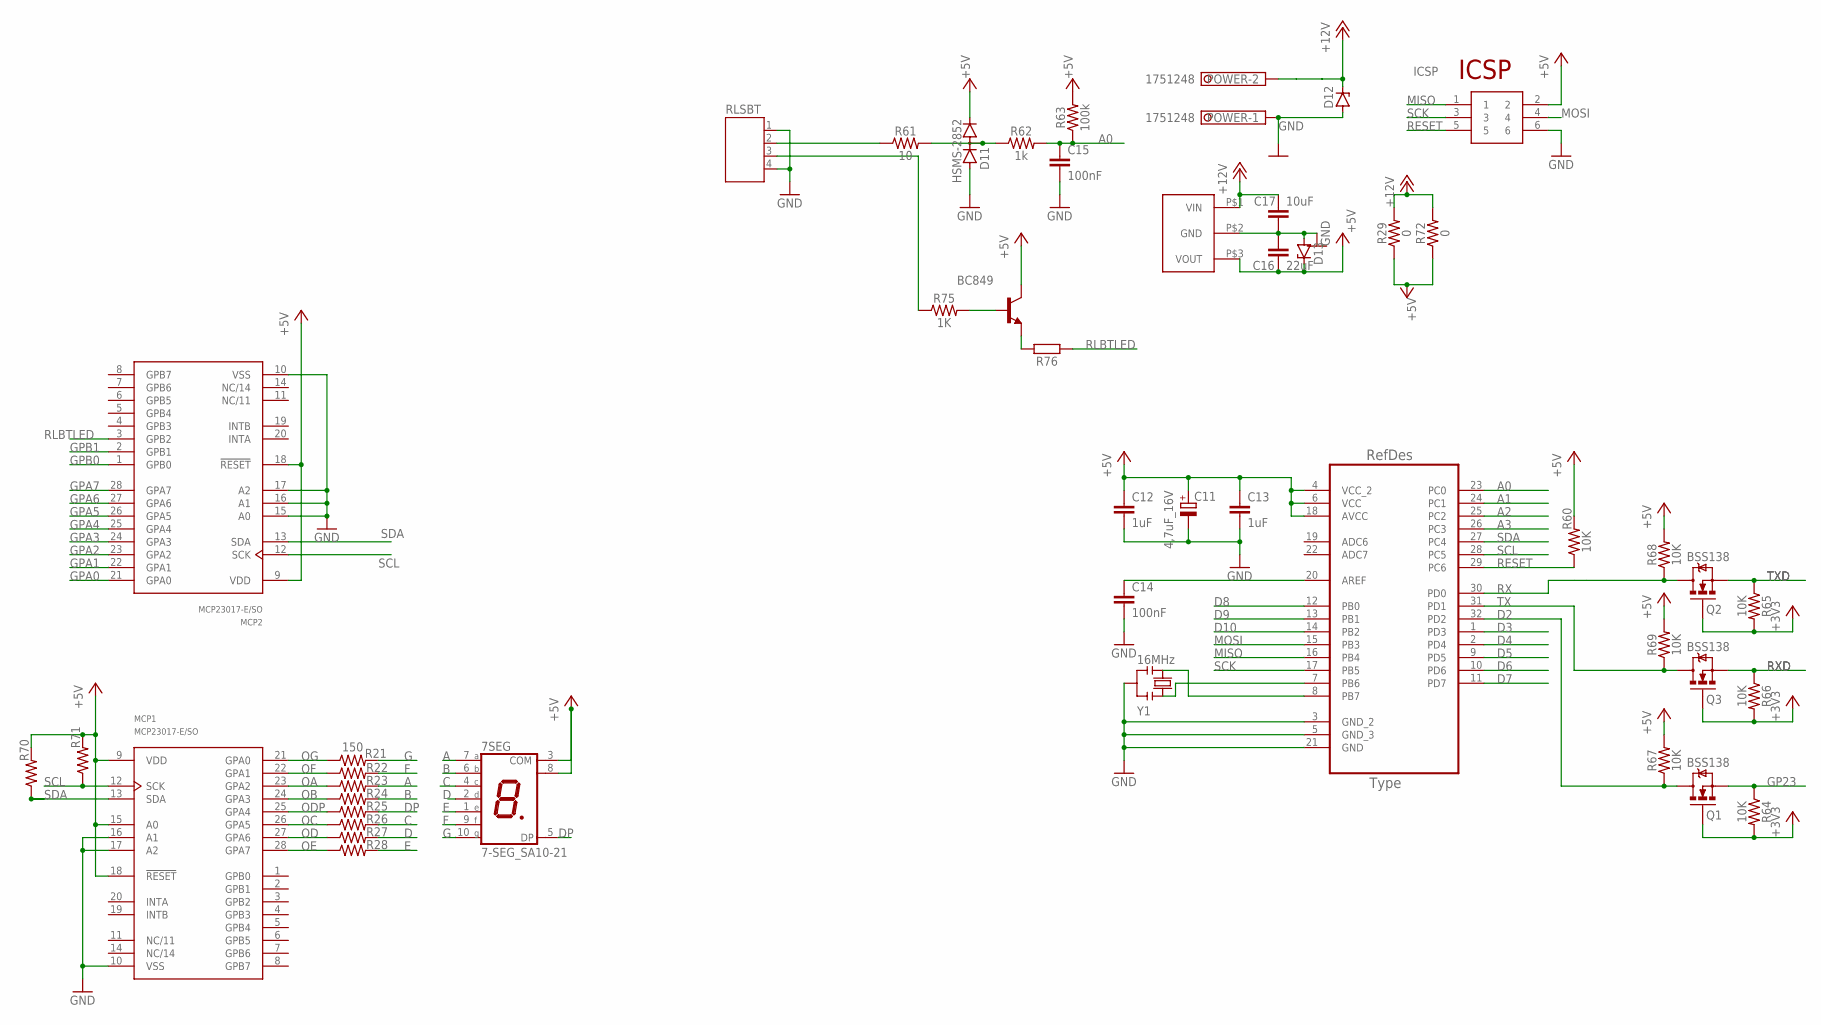
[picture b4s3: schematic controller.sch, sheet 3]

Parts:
7SEG: 7-SEG_SA10-21; SA10-21
C11: 4,7uF_16V; TAN-A
C12, C13: 1uF; C0603-ROUND
C14: 100nF; C0603-ROUND
C15: 100nF; C0805
C16: 22uF; C0805
C17: 10uF; C0805
D11: HSMS-2852; SOT23
D12, D13: ZENER-DIODESMB; SMB
ICSP: 61200621621; SHDR6W64P254_2X3_1528X910X910P
MCP1, MCP2: MCP23017-E/SO; SOIC28
POWER: 1751248
Q1, Q2, Q3: BSS138; SOT23-3
R21, R22, R23, R24, R25, R26, R27, R28: 150; 0805
R29, R72: 0; 0805
R60, R64, R65, R66, R67, R68, R69: 10K; 0805
R61: 10; 0805
R62: 1k; 0805
R63: 100k; 0805
R70, R71: 0805
R75: 1K; 0805
R76: 50; R2512
RLSBT: JST-PH4
T11: BC849; SOT23
U1: ATMEGA328P-AU; QFP80P900X900X120-32N
U$5: GAPTECCLC78; GAPTECLC78
Y1: 16MHz; RESONATOR

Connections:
+3V3: Q1.1 (G), Q2.1 (G), Q3.1 (G), R64.2, R65.2, R66.2; also elsewhere on the board
+5V: 7SEG.3 (COM), 7SEG.8 (COM), C11.1 (+), C12.1, C13.1, C16.2, D11.2 (C), D13.C, ICSP.2, MCP1.9 (VDD), MCP1.15 (A0), MCP1.18 (!RESET), MCP2.9 (VDD), MCP2.18 (!RESET), R29.1, R60.2, R63.2, R67.2, R68.2, R69.2, R70.2, R71.2, R72.1, T11.3 (C), U1.4 (VCC_2), U1.6 (VCC), U1.18 (AVCC), U$5.P$3 (VOUT); also elsewhere on the board
+12V: C17.1, D12.C, POWER.2, R29.2, R72.2, U$5.P$1 (VIN)
A: 7SEG.7 (A), R23.2
A0: C15.1, R62.2, R63.1, U1.23 (PC0)
A1: U1.24 (PC1); also elsewhere on the board
A2: U1.25 (PC2)
A3: U1.26 (PC3); also elsewhere on the board
B: 7SEG.6 (B), R24.2
C: 7SEG.4 (C), R26.2
D: 7SEG.2 (D), R27.2
D2: Q1.3 (D), R67.1, U1.32 (PD2)
D3: U1.1 (PD3); also elsewhere on the board
D4: U1.2 (PD4); also elsewhere on the board
D5: U1.9 (PD5); also elsewhere on the board
D6: U1.10 (PD6); also elsewhere on the board
D7: U1.11 (PD7); also elsewhere on the board
D8: U1.12 (PB0); also elsewhere on the board
D9: U1.13 (PB1); also elsewhere on the board
D10: U1.14 (PB2); also elsewhere on the board
DP: 7SEG.5 (DP), R25.2
E: 7SEG.1 (E), R28.2
F: 7SEG.9 (F), R22.2
G: 7SEG.10 (G), R21.2
GND: C11.2 (-), C12.2, C13.2, C14.2, C15.2, C16.1, C17.2, D11.1 (A), D12.A, D13.A, ICSP.6, MCP1.10 (VSS), MCP1.16 (A1), MCP1.17 (A2), MCP2.10 (VSS), MCP2.15 (A0), MCP2.16 (A1), MCP2.17 (A2), POWER.1, RLSBT.1, RLSBT.4, U1.3 (GND_2), U1.5 (GND_3), U1.21 (GND), U$5.P$2 (GND), Y1.2; also elsewhere on the board
GP23: Q1.2 (S), R64.1; also elsewhere on the board
GPA0: MCP2.21 (GPA0); also elsewhere on the board
GPA1: MCP2.22 (GPA1); also elsewhere on the board
GPA2: MCP2.23 (GPA2); also elsewhere on the board
GPA3: MCP2.24 (GPA3); also elsewhere on the board
GPA4: MCP2.25 (GPA4); also elsewhere on the board
GPA5: MCP2.26 (GPA5); also elsewhere on the board
GPA6: MCP2.27 (GPA6); also elsewhere on the board
GPA7: MCP2.28 (GPA7); also elsewhere on the board
GPB0: MCP2.1 (GPB0); also elsewhere on the board
GPB1: MCP2.2 (GPB1); also elsewhere on the board
MISO: ICSP.1, U1.16 (PB4)
MOSI: ICSP.4, U1.15 (PB3)
unnamed: U1.8 (PB7), Y1.3
unnamed: R75.2, T11.1 (B)
unnamed: R76.2, T11.2 (E)
unnamed: R75.1, RLSBT.3
unnamed: D11.3 (AC), R61.2, R62.1
unnamed: U1.7 (PB6), Y1.1
unnamed: C14.1, U1.20 (AREF)
OA: MCP1.23 (GPA2), R23.1
OB: MCP1.24 (GPA3), R24.1
OC: MCP1.26 (GPA5), R26.1
OD: MCP1.27 (GPA6), R27.1
ODP: MCP1.25 (GPA4), R25.1
OE: MCP1.28 (GPA7), R28.1
OF: MCP1.22 (GPA1), R22.1
OG: MCP1.21 (GPA0), R21.1
RESET: ICSP.5, R60.1, U1.29 (PC6)
RLBTLED: MCP2.3 (GPB2), R76.1
RLSBT: R61.1, RLSBT.2
RX: Q2.3 (D), R68.1, U1.30 (PD0)
RXD: Q3.2 (S), R66.1; also elsewhere on the board
SCK: ICSP.3, U1.17 (PB5)
SCL: MCP1.12 (SCK), MCP2.12 (SCK), R71.1, U1.28 (PC5)
SDA: MCP1.13 (SDA), MCP2.13 (SDA), R70.1, U1.27 (PC4)
TX: Q3.3 (D), R69.1, U1.31 (PD1)
TXD: Q2.2 (S), R65.1; also elsewhere on the board

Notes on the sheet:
ICSP

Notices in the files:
parts and their libraries:
SparkFun-Resistors: Licensing: Creative Commons ShareAlike 4.0 International - https://creativecommons.org/licenses/by-sa/4.0
SparkFun-Aesthetics: Licensing: CC v3.0 Share-Alike You are welcome to use this library for commercial purposes.
SparkFun-Aesthetics: Released under the Creative Commons
